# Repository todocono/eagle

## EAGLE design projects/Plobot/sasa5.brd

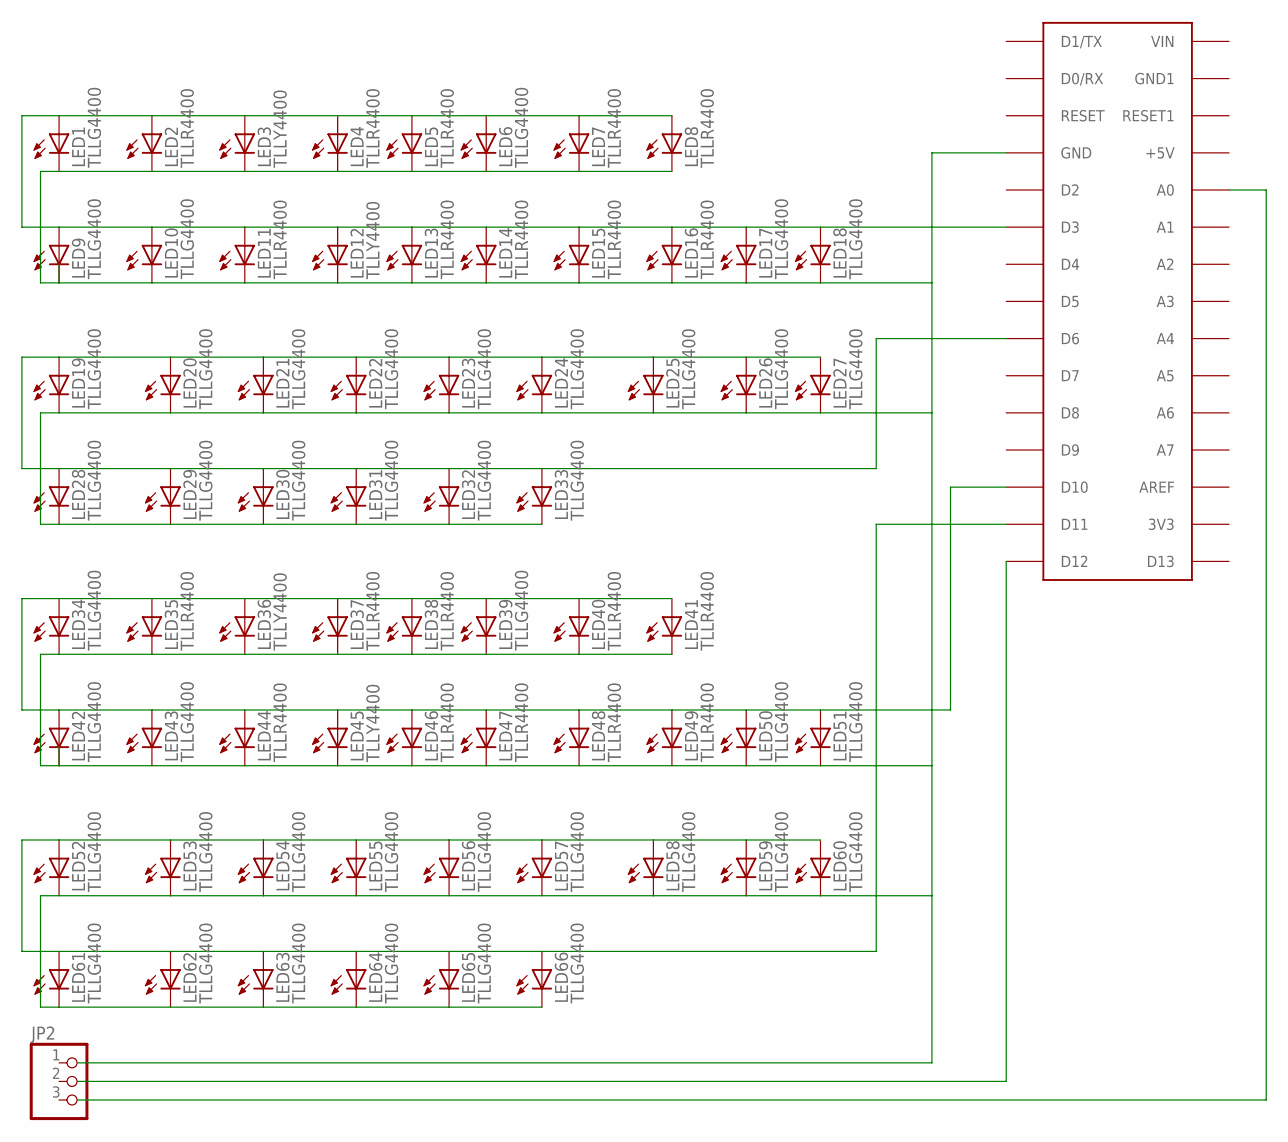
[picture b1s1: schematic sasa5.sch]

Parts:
JP2: PINHD-1X3; 1X03
LED1, LED6, LED9, LED10, LED17, LED18, LED19, LED20, LED21, LED22, LED23, LED24, LED25, LED26, LED27, LED28, LED29, LED30, LED31, LED32, LED33, LED34, LED39, LED42, LED43, LED50, LED51, LED52, LED53, LED54, LED55, LED56, LED57, LED58, LED59, LED60, LED61, LED62, LED63, LED64, LED65, LED66: TLLG4400; LED3MM
LED2, LED4, LED5, LED7, LED8, LED11, LED13, LED14, LED15, LED16, LED35, LED37, LED38, LED40, LED41, LED44, LED46, LED47, LED48, LED49: TLLR4400; LED3MM
LED3, LED12, LED36, LED45: TLLY4400; LED3MM
U$4: ARDUINONANO; PDIP-32

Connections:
unnamed: LED19.A, LED20.A, LED21.A, LED22.A, LED23.A, LED24.A, LED25.A, LED26.A, LED27.A, LED28.A, LED29.A, LED30.A, LED31.A, LED32.A, LED33.A, U$4.D6
unnamed: LED34.A, LED35.A, LED36.A, LED37.A, LED38.A, LED39.A, LED40.A, LED41.A, LED42.A, LED43.A, LED44.A, LED45.A, LED46.A, LED47.A, LED48.A, LED49.A, LED50.A, LED51.A, U$4.D10
unnamed: LED1.A, LED2.A, LED3.A, LED4.A, LED5.A, LED6.A, LED7.A, LED8.A, LED9.A, LED10.A, LED11.A, LED12.A, LED13.A, LED14.A, LED15.A, LED16.A, LED17.A, LED18.A, U$4.D3
unnamed: LED52.A, LED53.A, LED54.A, LED55.A, LED56.A, LED57.A, LED58.A, LED59.A, LED60.A, LED61.A, LED62.A, LED63.A, LED64.A, LED65.A, LED66.A, U$4.D11
unnamed: LED1.K (C), LED2.K (C), LED3.K (C), LED4.K (C), LED5.K (C), LED6.K (C), LED7.K (C), LED8.K (C), LED9.K (C), LED10.K (C), LED11.K (C), LED12.K (C), LED13.K (C), LED14.K (C), LED15.K (C), LED16.K (C), LED17.K (C), LED18.K (C), LED19.K (C), LED20.K (C), LED21.K (C), LED22.K (C), LED23.K (C), LED24.K (C), LED25.K (C), LED26.K (C), LED27.K (C), LED28.K (C), LED29.K (C), LED30.K (C), LED31.K (C), LED32.K (C), LED33.K (C), LED34.K (C), LED35.K (C), LED36.K (C), LED37.K (C), LED38.K (C), LED39.K (C), LED40.K (C), LED41.K (C), LED42.K (C), LED43.K (C), LED44.K (C), LED45.K (C), LED46.K (C), LED47.K (C), LED48.K (C), LED49.K (C), LED50.K (C), LED51.K (C), LED52.K (C), LED53.K (C), LED54.K (C), LED55.K (C), LED56.K (C), LED57.K (C), LED58.K (C), LED59.K (C), LED60.K (C), LED61.K (C), LED62.K (C), LED63.K (C), LED64.K (C), LED65.K (C), LED66.K (C), U$4.GND

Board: 2 copper layers, 68 parts (0 on the bottom side), 5 nets, no tracks yet.

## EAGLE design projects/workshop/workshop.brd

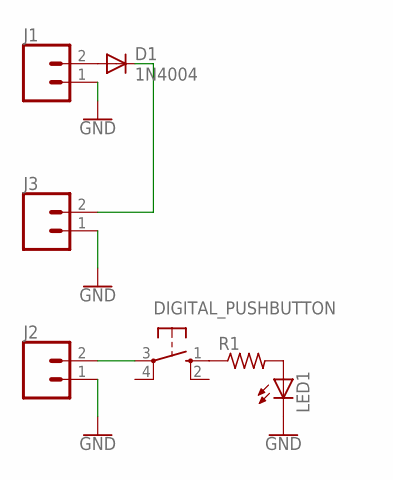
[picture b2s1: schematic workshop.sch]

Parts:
D1: 1N4004; DO41-10
DIGITAL_PUSHBUTTON: 10-XX; B3F-10XX
J1, J2, J3: CONN_02; 1X02
LED1: LED5MM
R1: R-US_0309/12; 0309/12

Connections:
GND: J1.1, J2.1, J3.1, LED1.K (C)
unnamed: LED1.A, R1.2
unnamed: DIGITAL_PUSHBUTTON.3, J2.2
unnamed: D1.A, J1.2
unnamed: D1.C, J3.2
unnamed: DIGITAL_PUSHBUTTON.1 (S), R1.1

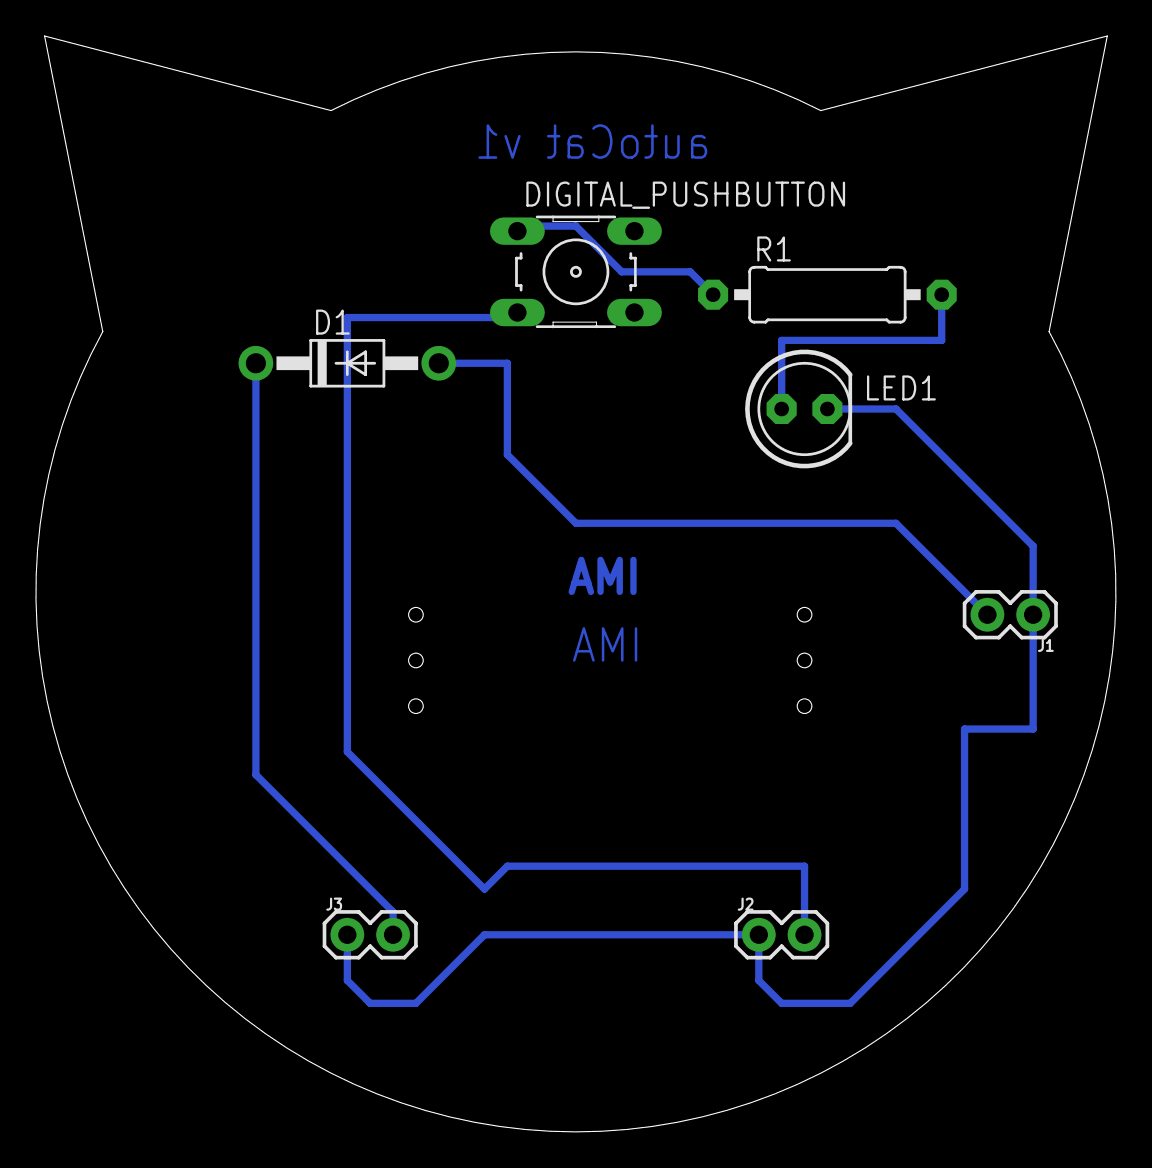
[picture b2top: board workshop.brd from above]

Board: 2 copper layers, 60.0 x 60.9 mm, 7 parts (0 on the bottom side), 6 nets.

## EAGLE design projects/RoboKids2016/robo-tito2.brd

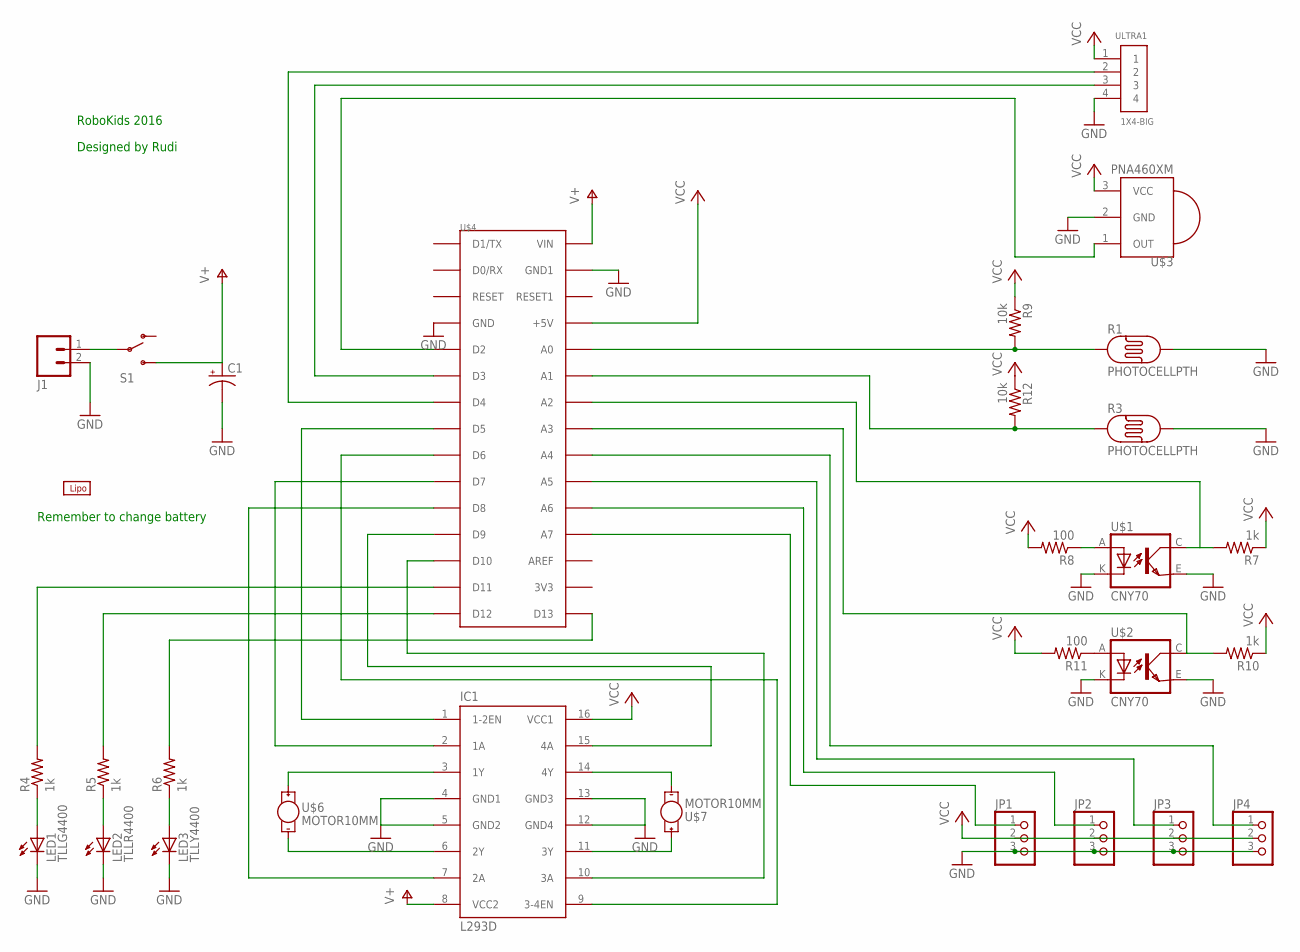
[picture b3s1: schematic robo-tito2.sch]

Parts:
C1: CPOL-USE10-20; EB20D
IC1: L293D; DIL16
J1: M02-JST-2-PTH-NO_SILK; JST-2-PTH-NS
JP1, JP2, JP3, JP4: PINHD-1X3; 1X03
LED1: TLLG4400; LED3MM
LED2: TLLR4400; LED3MM
LED3: TLLY4400; LED3MM
R1, R3: PHOTOCELLPTH; PHOTOCELL
R4, R5, R6, R7, R10: 1k; 0207/12
R8, R11: 100; 0207/12
R9, R12: 10k; 0207/12
S1: SWITCH-SPDTPTH2; SWITCHE-DPDT
U$1, U$2: CNY70; 4
U$3: PNA460XM
U$4: ARDUINONANO; PDIP-32
U$5: LIPO-OUTLINE2000; LIPO-2000
U$6, U$7: MOTOR10MM; VIBE-MOTOR-10MM
ULTRA1: 1X4-BIG; 1X04-BIG

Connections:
GND: C1.-, IC1.4 (GND1), IC1.5 (GND2), IC1.12 (GND4), IC1.13 (GND3), J1.2, JP1.3, JP2.3, JP3.3, JP4.3, LED1.K (C), LED2.K (C), LED3.K (C), R1.2, R3.2, U$1.E (EMI), U$1.K (C), U$2.E (EMI), U$2.K (C), U$3.2 (GND), U$4.GND, U$4.GND1, ULTRA1.4
unnamed: LED1.A, R4.1
unnamed: LED2.A, R5.1
unnamed: LED3.A, R6.1
unnamed: IC1.2 (1A), U$4.D7
unnamed: IC1.7 (2A), U$4.D8
unnamed: IC1.15 (4A), U$4.D9
unnamed: IC1.10 (3A), U$4.D10
unnamed: IC1.1 (1-2EN), U$4.D5
unnamed: IC1.9 (3-4EN), U$4.D6
unnamed: IC1.3 (1Y), U$6.+
unnamed: IC1.6 (2Y), U$6.-
unnamed: IC1.14 (4Y), U$7.-
unnamed: IC1.11 (3Y), U$7.+
unnamed: R4.2, U$4.D11
unnamed: R5.2, U$4.D12
unnamed: R6.2, U$4.D13
unnamed: R7.2, U$1.C (COL), U$4.A2
unnamed: R11.1, U$2.A
unnamed: U$3.1 (OUT), U$4.D2
unnamed: J1.1, S1.2
unnamed: R8.1, U$1.A
unnamed: JP1.1, U$4.A7
unnamed: R1.1, R9.2, U$4.A0
unnamed: R3.1, R12.2, U$4.A1
unnamed: R10.2, U$2.C (COL)
unnamed: U$4.D4, ULTRA1.2
unnamed: U$4.D3, ULTRA1.3
unnamed: JP2.1, U$4.A6
unnamed: JP3.1, U$4.A5
unnamed: JP4.1, U$4.A4
V+: C1.+, IC1.8 (VCC2), S1.3 (S), U$4.VIN
VCC: IC1.16 (VCC1), JP1.2, JP2.2, JP3.2, JP4.2, R7.1, R8.2, R9.1, R10.1, R11.2, R12.1, U$3.3 (VCC), U$4.+5V, ULTRA1.1

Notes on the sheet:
Designed by Rudi
RoboKids 2016
Remember to change battery

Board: 2 copper layers, 30 parts (0 on the bottom side), 33 nets, no tracks yet.

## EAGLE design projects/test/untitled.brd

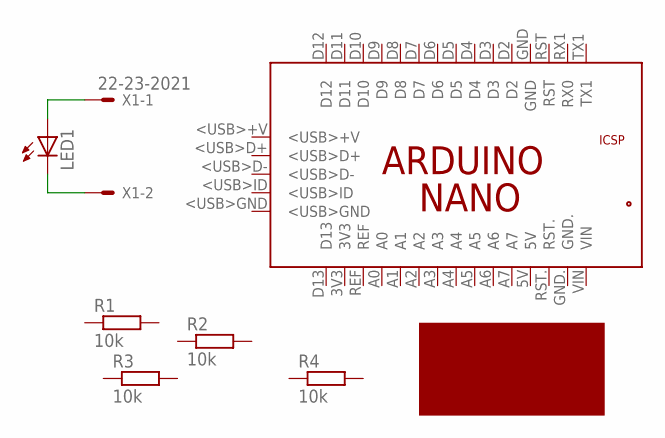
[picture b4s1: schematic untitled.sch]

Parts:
LED1: LED; SMARTLED-TTW
PCB1: ARDUINO_NANO
R1, R2, R3, R4: 10k; 0207/10
U$1: MOTOR_N20
X1: 22-23-2021

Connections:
unnamed: LED1.A@1 (A), X1.1
unnamed: LED1.C@1 (C), X1.2

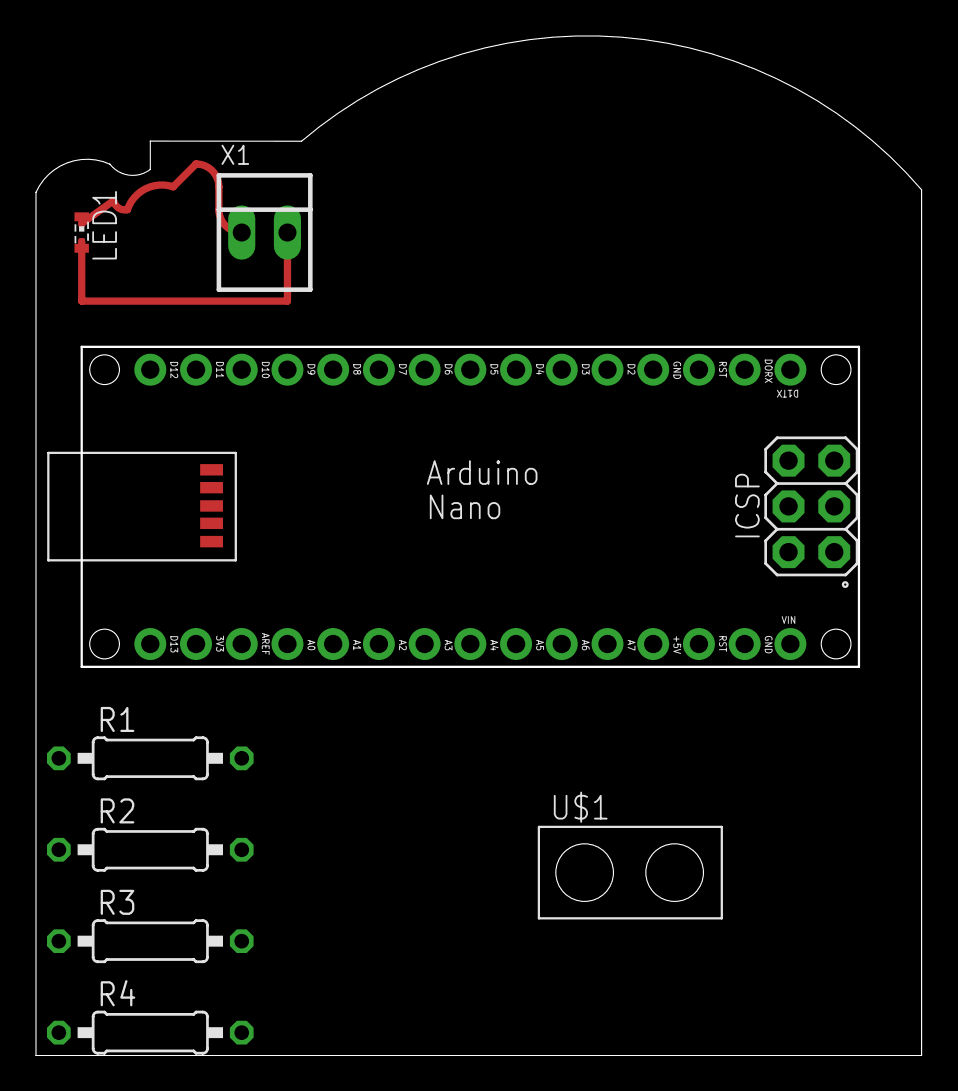
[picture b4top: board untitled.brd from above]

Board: 2 copper layers, 49.1 x 56.5 mm, 8 parts (0 on the bottom side), 2 nets.

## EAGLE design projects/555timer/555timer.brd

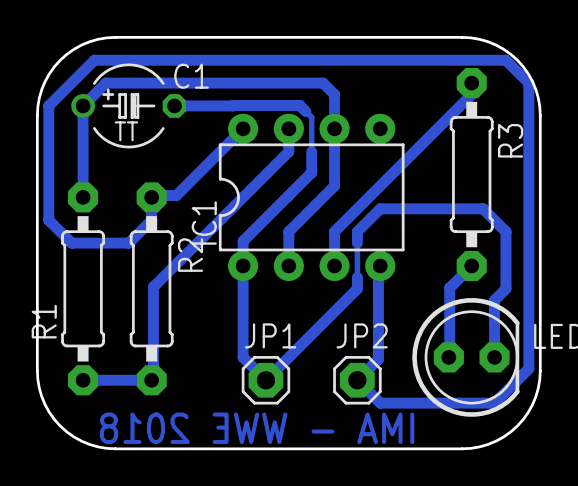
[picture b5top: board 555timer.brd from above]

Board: 2 copper layers, 27.9 x 22.9 mm, 8 parts (0 on the bottom side), 6 nets.

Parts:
C1: 1uF; TAP5-45
IC1: LM555N; DIL08-ROUND
JP1: GND; 1X01
JP2: VCC; 1X01
LED1: LED5MM
R1: 470k; 0207/10
R2, R3: 1k; 0207/10

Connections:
GND: C1.-, IC1.1, JP1.1, LED1.K
unnamed: IC1.3, R3.1
unnamed: LED1.A, R3.2
unnamed: C1.+, IC1.2, IC1.6, R1.2
unnamed: IC1.7, R1.1, R2.2
VCC: IC1.4, IC1.8, JP2.1, R2.1

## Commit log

2020-06-04 uploaded june 2020

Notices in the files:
parts and their libraries:
SparkFun-Connectors: Licensing: Creative Commons ShareAlike 4.0 International - https://creativecommons.org/licenses/by-sa/4.0
